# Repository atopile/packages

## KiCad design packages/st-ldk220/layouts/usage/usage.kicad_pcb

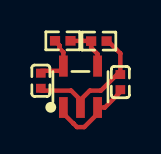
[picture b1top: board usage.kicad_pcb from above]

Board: 2 copper layers, 5 parts (0 on the bottom side), 5 nets.

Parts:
C1, C2: 1µF ±10%; C0402
R1: 2.61kΩ ±1%; R0402
R2: 1.47kΩ ±1%; R0402
U1: SOT-23-5_L3.0-W1.7-P0.95-LS2.8-BL

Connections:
hv: C2.1, R1.1, U1.5
lv: C2.2, R2.2
power_in-hv: C1.1, U1.1, U1.3
power_in-lv: C1.2, U1.2
ref_out-hv: R1.2, R2.1, U1.4

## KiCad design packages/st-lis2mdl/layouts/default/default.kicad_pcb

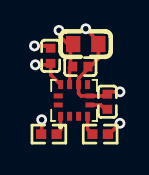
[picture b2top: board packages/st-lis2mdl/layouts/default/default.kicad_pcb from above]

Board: 2 copper layers, 7 parts (0 on the bottom side), 6 nets.

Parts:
C1: 2.2e-F; C0402
C2: 9.999F; C0603
C3, C4: 1F; C0402
R1, R2: 10000Ω; R0402
U1: LGA-12_L2.0-W2.0-P0.50-BL

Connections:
MOSI: R2.2, U1.4
SCL: R1.2, U1.1
hv: C1.1, U1.5
lv: C1.2, C2.2, C3.2, C4.2, U1.6, U1.8
vdd_cap_10uf-power-hv: C2.1, C3.1, U1.9
vddio_cap_100nf-power-hv: C4.1, R1.1, R2.1, U1.10

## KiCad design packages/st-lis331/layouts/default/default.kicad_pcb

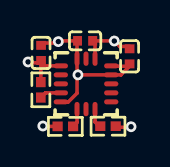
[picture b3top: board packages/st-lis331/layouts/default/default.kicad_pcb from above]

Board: 2 copper layers, 7 parts (0 on the bottom side), 6 nets.

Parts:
C1, C2, C3: 1F; C0402
R1, R2, R3: 10000Ω; R0402
U1: LGA-16_L3.0-W3.0-P0.50-TL

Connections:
CS: R1.2, U1.8
SCL: R2.1, U1.4
SDA: R3.1, U1.6
hv: C3.1, R1.1, R2.2, R3.2, U1.1
lv: C1.2, C2.2, C3.2, U1.5, U1.7, U1.12, U1.13, U1.16
vdd_caps[1]-power-hv: C1.1, C2.1, U1.14

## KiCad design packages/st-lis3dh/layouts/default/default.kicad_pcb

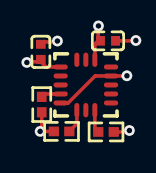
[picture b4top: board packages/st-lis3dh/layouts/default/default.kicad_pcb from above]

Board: 2 copper layers, 6 parts (0 on the bottom side), 6 nets.

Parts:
C1, C2: 1±10.0%F; C0402
R1, R2, R3: 10000±1.0%Ω; R0402
U1: LGA-16_L3.0-W3.0-P0.50-TL

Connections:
CS: R1.2, U1.8
MOSI: R3.2, U1.6
SCL: R2.2, U1.4
decoupling_caps[0]-power-hv: C1.1, U1.14
hv: C2.1, R1.1, R2.1, R3.1, U1.1
lv: C1.2, C2.2, U1.5, U1.7, U1.12
